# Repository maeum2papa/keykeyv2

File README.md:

# keykeyv2 제작 가이드

---

## 개발 계기
손목 터널 증후군 통증을 완화하기 위한 목적으로 개발
- 손목이 들리거나 꺽이는 걸 방지하기 위해 낮은 키보드를 사용
- 손목의 자연스러운 형태를 유지하기 위해 반으로 자름
- 개발자 주로 사용하는 키를 서로 가깝게 배치

---

## 키보드 특징

- **스플릿 키보드** (좌/우 분리형)
- **각 사이드 5행 6열** = 총 60키 (매트릭스)
- **왼쪽 사이드가 마스터**
- **방향키 4개**(다이렉트 핀, 5방향 네비게이션 스위치)
- **캡스락 LED** 1개
- **Vial-QMK** 사용 (GUI로 키맵 변경 가능)

---

## 필요 부품

### 🔲 프로세서
| 항목 | 수량 | 상세 |
|---|---|---|
| RP2040-Zero | 2개 | 좌/우 각 1개. 옆면 캐스텔레이티드(Castellated) 핀 납땜 계획. USB-C 내장 |

> ⚠️ 반드시 정품 구매

### ⌨️ 스위치 & 소켓
| 항목 | 수량 | 상세 |
|---|---|---|
| Kailh Choc v1 (1350) 스위치 | 60개 | 
| Choc v1 전용 핫스왑 소켓 | 60개 | 반드시 Choc v1 전용 규격 확인 (MX 소켓과 호환 안됨) |

### 🔵 다이오드
| 항목 | 수량 | 상세 |
|---|---|---|
| 1N4148W SMD 다이오드 | 60개 |

### 🕹️ 방향키 & 인코더
| 항목 | 수량 | 상세 |
|---|---|---|
| 5-Way 네비게이션 스위치 | 1개 | 상/하/좌/우/센터 클릭 지원 모델. PCB에 45도 회전 배치 권장 |

> ⚠️ 5방향 스위치를 정사각형으로 배치하면 대각 방향으로 눌러야 상하좌우 동작함.
> PCB 설계 시 반드시 **45도 회전(마름모) 배치** 권장

### 💡 상태 표시 LED
| 항목 | 수량 | 상세 |
|---|---|---|
| 3mm LED | 2개 | 각 사이드 1개. Caps Lock 활성 표시용 |
| 저항 330Ω | 2개 | LED 보호용. 각 사이드 GP28과 LED 사이에 직렬 연결 |

### 🔌 통신 & 연결
| 항목 | 수량 | 상세 |
|---|---|---|
| PJ-320A TRRS 잭 | 2개 | 반드시 4극 전용 (3극 사용 시 쇼트 위험) |
| 4극 TRRS 케이블 | 1개 | 양쪽 유선 연결용 |
| 저항 1kΩ | 2개 | GP0 ↔ TRRS Ring 사이 각 사이드 1개씩 (통신 보호용) |

---

## PCB 주문 제작
샘플 PCB를 제작 해주는 곳에서는 어디서든 가능 (JLC PCB, 샘플 PCB ...)

### 1. 거버 및 드릴 파일 다운로드
/last/keykeyv2.1_l.zip (왼쪽)
/last/keykeyv2.1_r.zip (오른쪽)

### 2. PCB 주문
keykeyv2.1_l.zip, keykeyv2.1_r.zip 파일을 업로드해서 주문

---

## 납땜

### 1. 납땜 위치
- 다이오드, 핫스왑 소켓 후면에 장착
- RP2024-zero, PJ-320A TRRS 잭, LED 앞면 장착

### 2. 다이오드 방향
- (|) 표시가 있는 방향이 양 사이드의 가운데를 향해야 함 (왼쪽 사이드에서는 오른쪽, 오른쪽 사이드에서는 왼쪽)

---

## 필요 프로그램 설치

### 1. 파일 다운로드
/last/keykeyv2_vial.uf2 다운로드

### 2. 각 사이드 마다 RP2024-zero 펌웨어 업로드
- 1. 모든 선 분리 후 USB만 단독으로 연결 (꼭 통신 케이블용 사용)
- 1. BOOT 버튼, RESET 버튼 동시에 누름
- 2. 1초 후 RESET 버튼에서 손때고 그 다음 1초 후 BOOT 버튼에서 손 땜
- 3. 외장 드라이버로 인식되면 keykeyv2_vial.uf2 파일 복사해서 저장
- 4. 자동으로 RP2024-zero 재부팅

---

## 작동 테스트

- 1. USB가 연결되지 않은 상태에서 TRRS선 연결
> ⚠️ USB가 연결된 상태에서 TRRS선 분리하면 고장남
- 2. USB 왼쪽 사이드에 연결
> 항상 왼쪽이 마스터

---

## 3D 프린터를 이용한 케이스 출력
/last/keykeyv2_case.3mf 다운로드 하여 출력

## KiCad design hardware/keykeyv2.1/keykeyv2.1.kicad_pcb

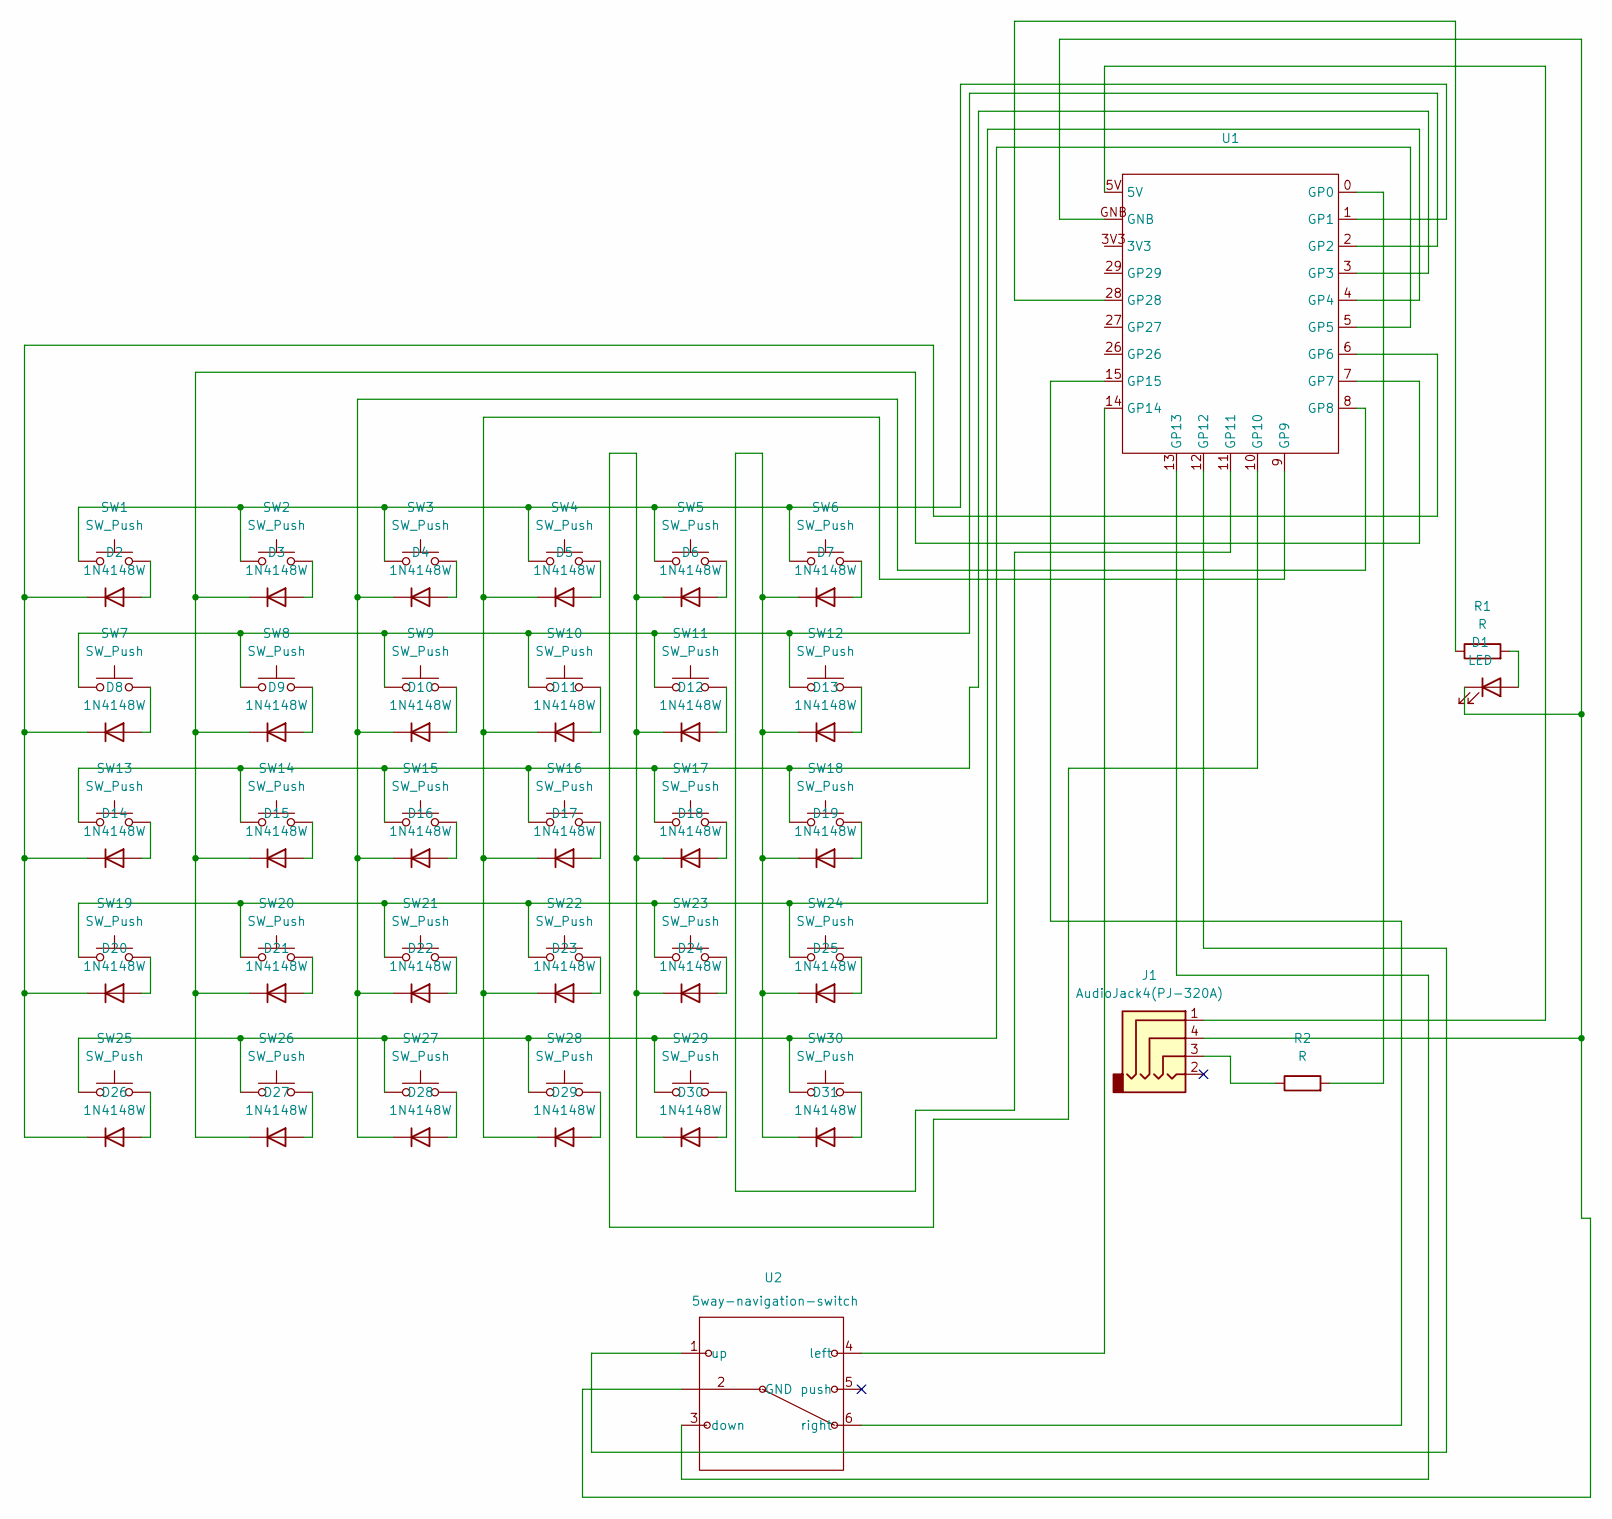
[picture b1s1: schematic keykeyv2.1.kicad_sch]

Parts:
D1: LED; LED_0805_2012Metric_Pad1.15x1.40mm_HandSolder
D2, D3, D4, D5, D6, D7, D8, D9, D10, D11, D12, D13, D14, D15, D16, D17, D18, D19, D20, D21, D22, D23, D24, D25, D26, D27, D28, D29, D30, D31: 1N4148W; D_SOD-123
J1: AudioJack4(PJ-320A); PJ-320A
R1, R2: R; R_0805_2012Metric_Pad1.20x1.40mm_HandSolder
SW1, SW2, SW3, SW4, SW5, SW6, SW7, SW8, SW9, SW10, SW11, SW12, SW13, SW14, SW15, SW16, SW17, SW18, SW19, SW20, SW21, SW22, SW23, SW24, SW25, SW26, SW27, SW28, SW29, SW30: SW_Push; SW_Hotswap_Kailh_Choc_V1V2_1.00u
U1: RP2040_Zero_Up_Mount
U2: 5way-navigation-switch

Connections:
unnamed: D1.2 (A), R1.2
unnamed: D1.1 (K), J1.4, U1.GNB, U2.2 (GND)
unnamed: D2.2 (A), SW1.2
unnamed: D3.2 (A), SW2.2
unnamed: D4.2 (A), SW3.2
unnamed: D5.2 (A), SW4.2
unnamed: D6.2 (A), SW5.2
unnamed: D7.2 (A), SW6.2
unnamed: D8.2 (A), SW7.2
unnamed: D9.2 (A), SW8.2
unnamed: D10.2 (A), SW9.2
unnamed: D4.1 (K), D10.1 (K), D16.1 (K), D22.1 (K), D28.1 (K), U1.8 (GP8)
unnamed: D11.2 (A), SW10.2
unnamed: D5.1 (K), D11.1 (K), D17.1 (K), D23.1 (K), D29.1 (K), U1.9 (GP9)
unnamed: D12.2 (A), SW11.2
unnamed: D6.1 (K), D12.1 (K), D18.1 (K), D24.1 (K), D30.1 (K), U1.10 (GP10)
unnamed: D13.2 (A), SW12.2
unnamed: D7.1 (K), D13.1 (K), D19.1 (K), D25.1 (K), D31.1 (K), U1.11 (GP11)
unnamed: D14.2 (A), SW13.2
unnamed: D2.1 (K), D8.1 (K), D14.1 (K), D20.1 (K), D26.1 (K), U1.6 (GP6)
unnamed: D15.2 (A), SW14.2
unnamed: D3.1 (K), D9.1 (K), D15.1 (K), D21.1 (K), D27.1 (K), U1.7 (GP7)
unnamed: D16.2 (A), SW15.2
unnamed: D17.2 (A), SW16.2
unnamed: D18.2 (A), SW17.2
unnamed: D19.2 (A), SW18.2
unnamed: D20.2 (A), SW19.2
unnamed: D21.2 (A), SW20.2
unnamed: D22.2 (A), SW21.2
unnamed: D23.2 (A), SW22.2
unnamed: D24.2 (A), SW23.2
unnamed: D25.2 (A), SW24.2
unnamed: D26.2 (A), SW25.2
unnamed: D27.2 (A), SW26.2
unnamed: D28.2 (A), SW27.2
unnamed: D29.2 (A), SW28.2
unnamed: D30.2 (A), SW29.2
unnamed: D31.2 (A), SW30.2
unnamed: J1.1, U1.5V
unnamed: J1.3, R2.1
unnamed: R2.2, U1.0 (GP0)
unnamed: SW1.1, SW2.1, SW3.1, SW4.1, SW5.1, SW6.1, U1.1 (GP1)
unnamed: SW7.1, SW8.1, SW9.1, SW10.1, SW11.1, SW12.1, U1.2 (GP2)
unnamed: SW13.1, SW14.1, SW15.1, SW16.1, SW17.1, SW18.1, U1.3 (GP3)
unnamed: SW19.1, SW20.1, SW21.1, SW22.1, SW23.1, SW24.1, U1.4 (GP4)
unnamed: SW25.1, SW26.1, SW27.1, SW28.1, SW29.1, SW30.1, U1.5 (GP5)
unnamed: U1.12 (GP12), U2.1 (up)
unnamed: U1.13 (GP13), U2.3 (down)
unnamed: U1.14 (GP14), U2.4 (left)
unnamed: U1.15 (GP15), U2.6 (right)
unnamed: R1.1, U1.28 (GP28)

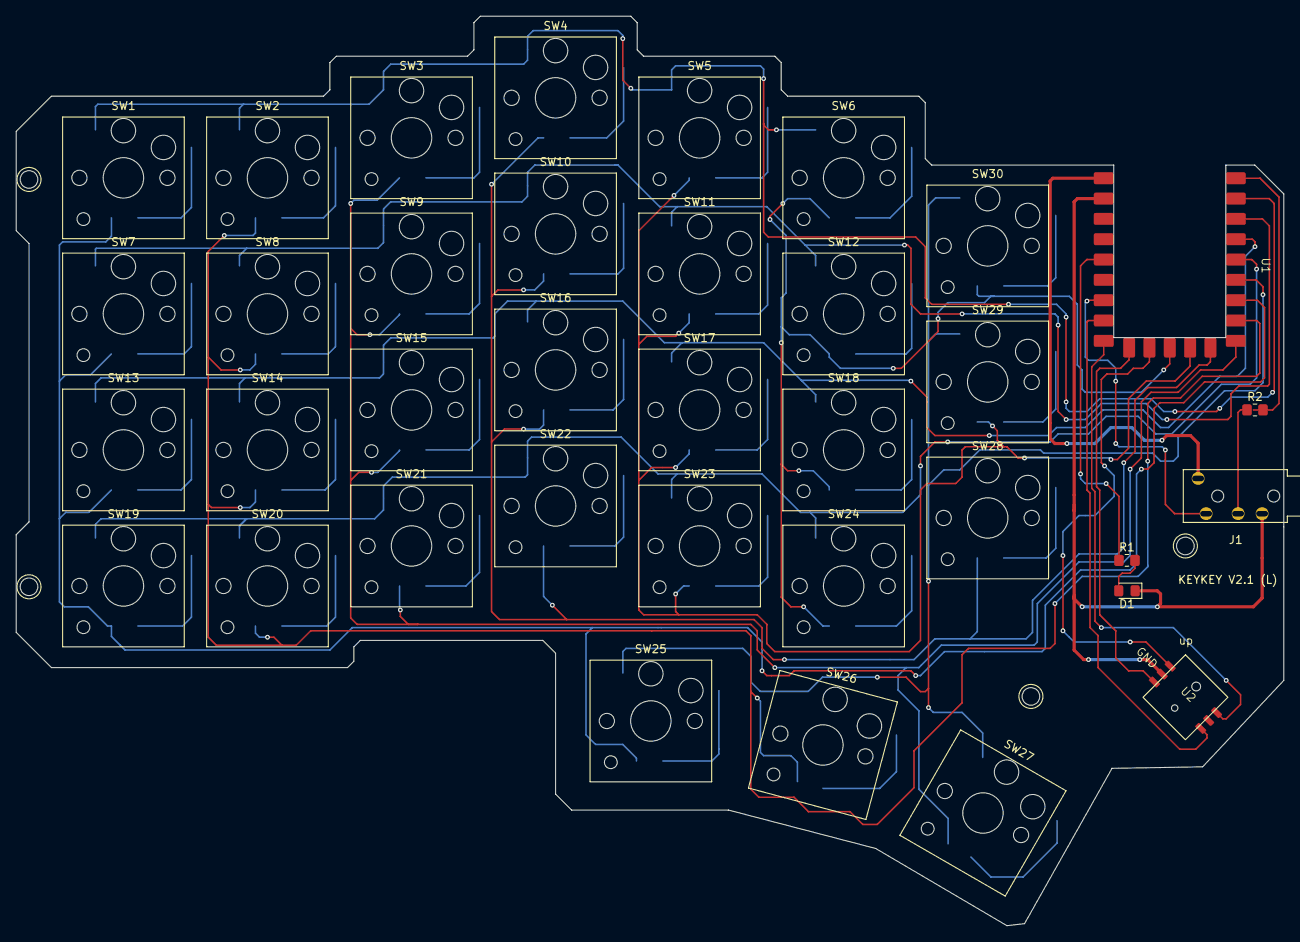
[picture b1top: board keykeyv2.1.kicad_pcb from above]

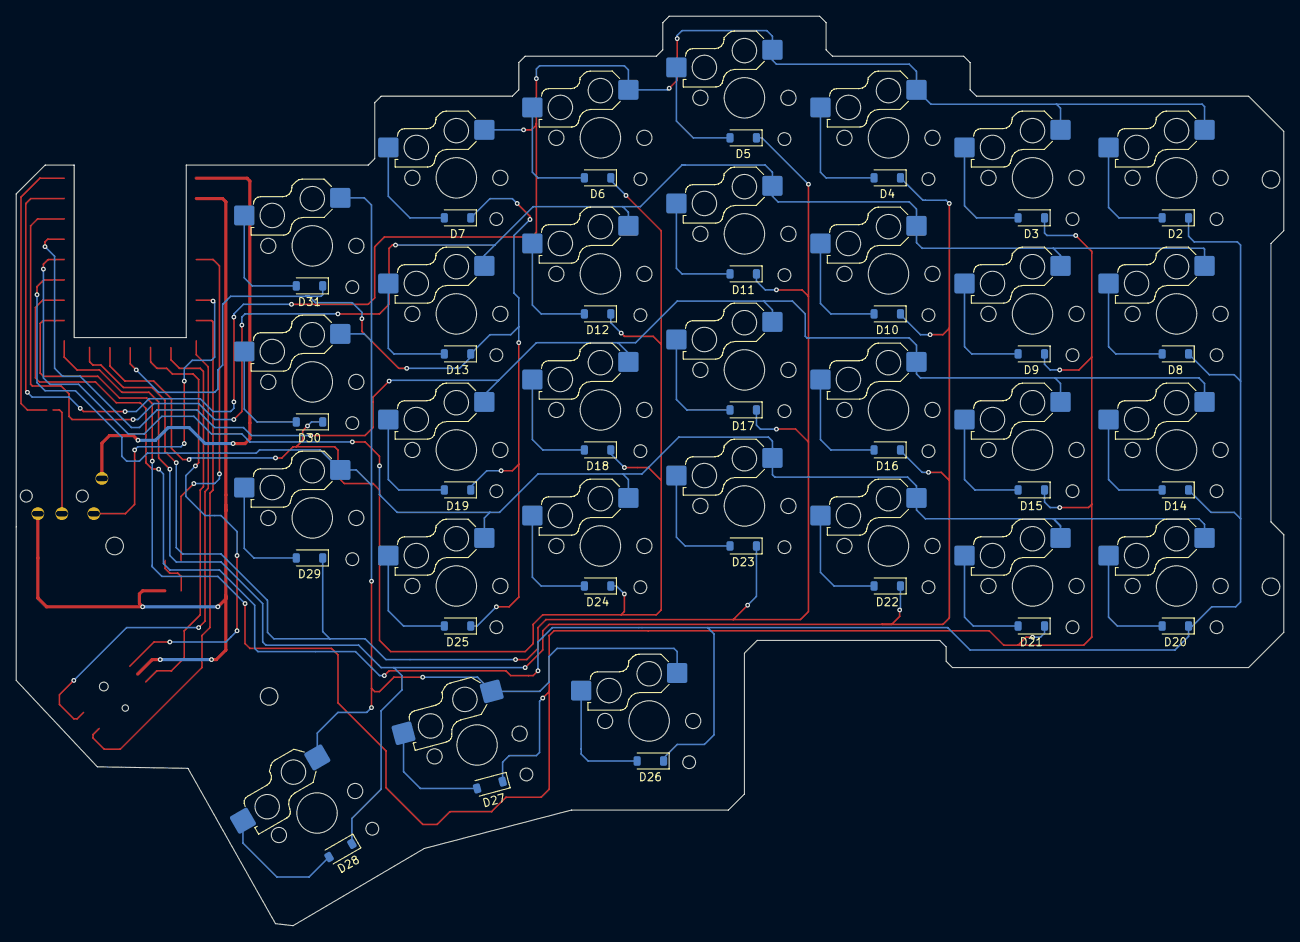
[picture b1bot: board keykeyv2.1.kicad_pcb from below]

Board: 2 copper layers, 158.4 x 113.6 mm, 66 parts (30 on the bottom side), 51 nets.

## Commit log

2026-04-29 setting .gitignore
2026-04-30 qmk-vial-real
2026-05-02 업데이트
2026-05-02 이미지 업로드
2026-05-03 3D 프린터 케이스 출력 파일 업데이트
2026-05-04 vial update
2026-05-08 kicad 파일 좌우 분리
